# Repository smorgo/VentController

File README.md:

# VentController
<p>Code and hardware resources for my IoT Vent Controller, intended to control automatic conservatory roof vents (but equally applicable to many similar use cases).</p>
<p>The system is based around the ESP8266 microcontroller. I'm currently using it in its SparkFun ESP8266 Thing guise, but the board could be reworked to suit any of the ESP12-derived boards out there.</p>
<p>You can find the Eagle schematic and board files in the Eagle folder.</p>
<p>Initially, I had intended to use the NodeMCU firmware for the ESP8266. However, that simply takes too much memory and caused immense frustration, so I've moved to using the Arduino IDE and programming in C++. The NodeMCU source files are just here for reference.</p>

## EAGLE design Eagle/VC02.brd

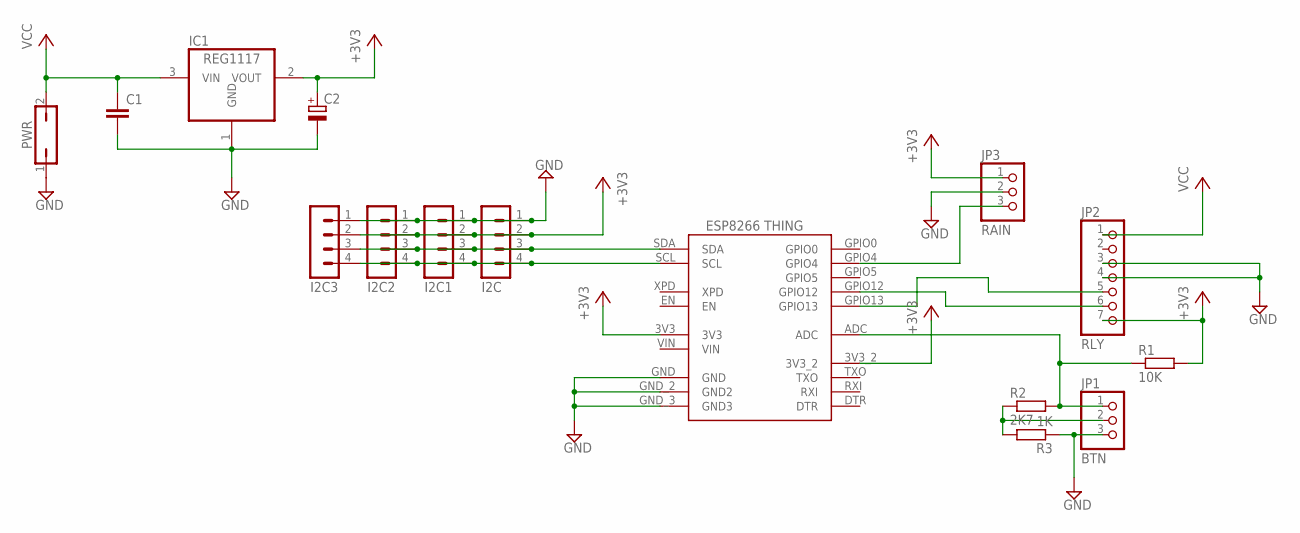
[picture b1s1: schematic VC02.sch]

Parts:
C1: C-EUC0603K; C0603K; MPN 0603YC104K4T2A
C2: CPOL-EUB; PANASONIC_B; MPN EEEFC1C220AR
I2C, I2C1, I2C2, I2C3: MA04-1
IC1: REG1117; SOT223; MPN LD1117S33TR
JP1: BTN; 1X03
JP2: RLY; 1X07
JP3: RAIN; 1X03
PWR: JP1Q; JP1; MPN 640452-2
R1: 10K; R0805; MPN CRCW080510K0FKEA
R2: 2K7; R0805; MPN CRCW08052K70FKEA
R3: 1K; R0805; MPN CRCW08051K00FKEA
U$1: ESP8266_THING

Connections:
+3V3: C2.+, I2C.2, I2C1.2, I2C2.2, I2C3.2, IC1.2 (VOUT), JP2.7, JP3.1, R1.2, U$1.3V3, U$1.3V3_2
GND: C1.2, C2.-, I2C.1, I2C1.1, I2C2.1, I2C3.1, IC1.1 (GND), JP1.3, JP2.3, JP2.4, JP3.2, PWR.1, R3.1, U$1.GND, U$1.GND_2 (GND2), U$1.GND_3 (GND3)
unnamed: JP2.6, U$1.GPIO12
unnamed: JP2.5, U$1.GPIO13
unnamed: JP3.3, U$1.GPIO4
unnamed: JP1.2, R2.1, R3.2
unnamed: JP1.1, R1.1, R2.2, U$1.ADC
unnamed: I2C.4, I2C1.4, I2C2.4, I2C3.4, U$1.SCL
unnamed: I2C.3, I2C1.3, I2C2.3, I2C3.3, U$1.SDA
VCC: C1.1, IC1.3 (VIN), JP2.1, PWR.2
VIN: U$1.VIN

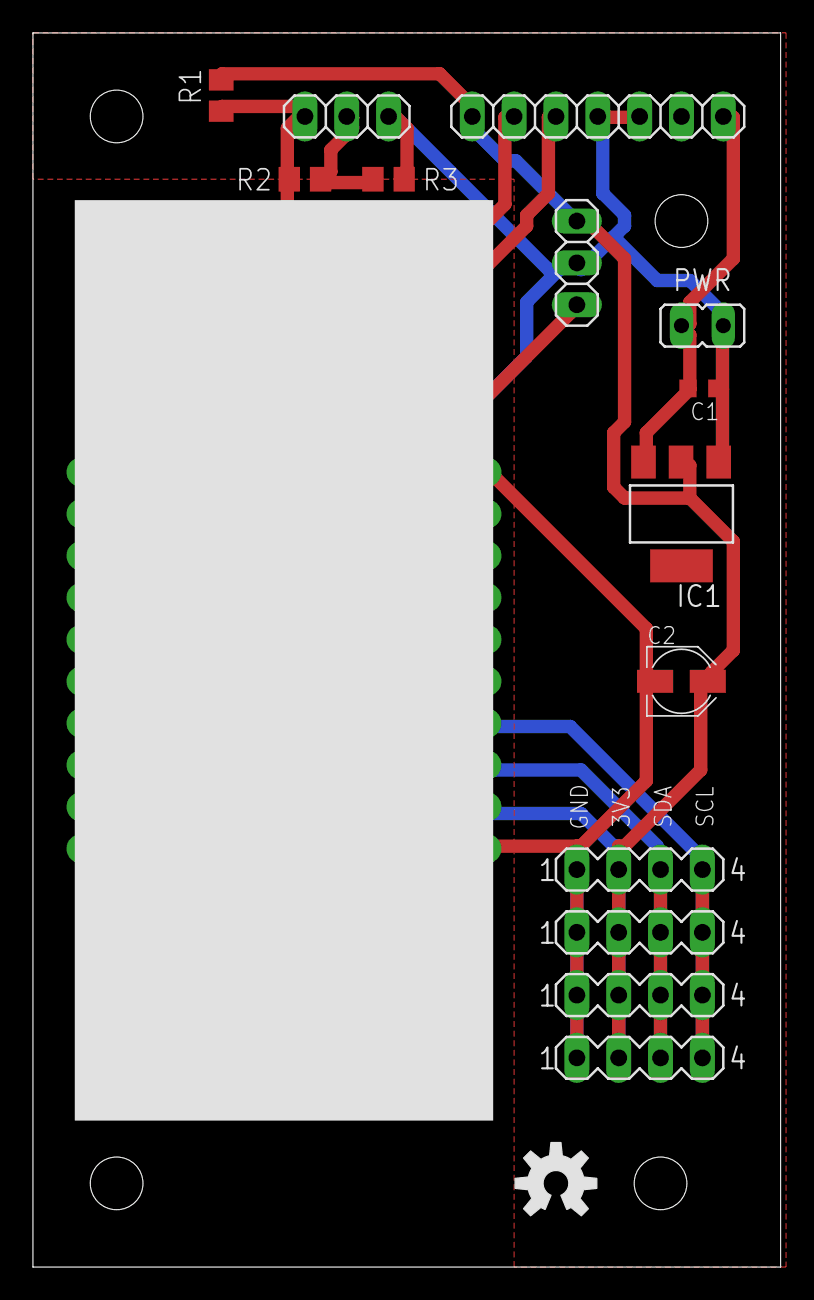
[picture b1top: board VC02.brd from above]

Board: 2 copper layers, 45.4 x 74.9 mm, 16 parts (0 on the bottom side), 10 nets.

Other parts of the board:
U$2: OSHW-LOGO-M

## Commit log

2015-07-16 Initial sensor code
2015-07-17 Migrating to modules
2015-08-06 Moved to Arduino sketch
2015-08-06 Removed commented-out code
2015-08-10 Sketch update
    Sensor code working. First version of actuator code added.
2015-08-10 Added boards and renamed NodeMCU files
2015-08-10 Added a little more detail.
2015-08-10 Formatting
2015-08-10 Typo
2015-08-13 Added vent relay control
    Vent relay now operates on boot to ensure that vents are closed. Also
    responds to message over MQTT to set vent position, though message
    format needs updating.
2015-08-23 Updated message formats & added Xamarin client

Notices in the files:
parts and their libraries:
SparkFun-Aesthetics: Licensing: Creative Commons ShareAlike 4.0 International - https://creativecommons.org/licenses/by-sa/4.0
